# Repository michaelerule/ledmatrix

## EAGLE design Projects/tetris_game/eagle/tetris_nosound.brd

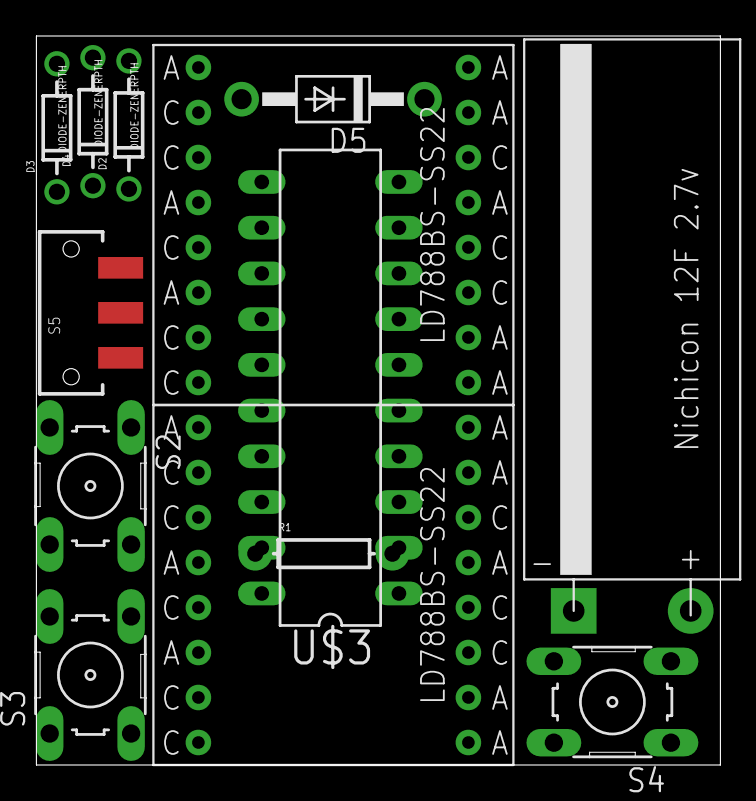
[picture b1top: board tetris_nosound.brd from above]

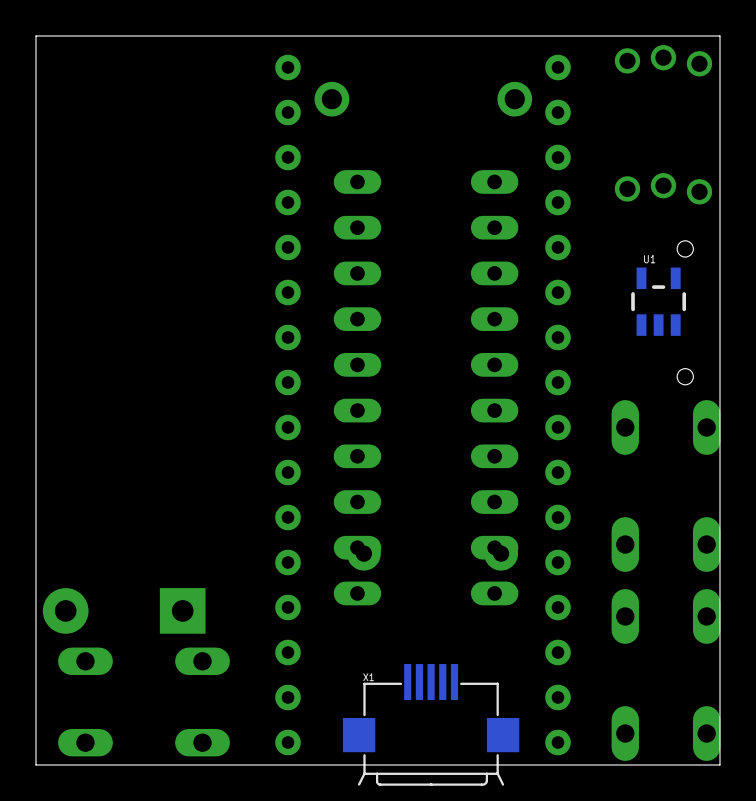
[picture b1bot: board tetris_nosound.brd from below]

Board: 2 copper layers, 38.0 x 40.5 mm, 15 parts (2 on the bottom side), 25 nets, no tracks yet.

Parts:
D2, D3, D4: DIODE-ZENERPTH; DIODE-ZENER
D5: 1N4004; DO41-10
R1: AXIAL-0.3
S2, S3, S4: B3F-10XX
S5: SWITCH-SPDT-SMD
U1: V_REG_LDOSMD; SOT23-5
U$1, U$2: LD788BS-SS22
U$3: TINY2313-*P*; DIL20
U$5: NICHICON_12F; NICHICON_10X30
X1: USB-MICROB

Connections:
unnamed: U$1.A4, U$2.C1, U$3.13
unnamed: U$1.A5, U$2.C2, U$3.14
unnamed: U$1.C6, U$2.A2, U$3.15
unnamed: U$1.A6, U$2.C3, U$3.16
unnamed: U$1.C7, U$2.A3, U$3.17
unnamed: U$1.A7, U$2.C4, U$3.19
unnamed: U$1.A8, U$2.C5, U$3.5
unnamed: U$1.C8, U$2.A1, U$3.18
unnamed: D5.C, R1.P$1, U$5.P$2
unnamed: U$1.C2, U$2.A5, U$3.3
unnamed: D2.P$2, U$1.A2, U$2.C6, U$3.6
unnamed: D3.P$2, U$1.C3, U$2.A6, U$3.7
unnamed: D4.P$2, U$1.A3, U$2.C7, U$3.8
unnamed: U$1.A1, U$2.C8, U$3.9
unnamed: U$1.C4, U$2.A7, U$3.11
unnamed: U$1.C5, U$2.A8, U$3.12
unnamed: D5.A, U$3.10
unnamed: S5.1, U1.5, U$5.P$1
unnamed: D2.P$1, S2.3, S2.4
unnamed: D3.P$1, S3.3, S3.4
unnamed: D4.P$1, S4.3, S4.4
unnamed: R1.P$2, U1.2, X1.GND
unnamed: U1.1, X1.D+, X1.D-, X1.VBUS
unnamed: S5.2, U$3.20
unnamed: S2.1, S2.2, S3.1, S3.2, S4.1, S4.2, U$1.C1, U$2.A4

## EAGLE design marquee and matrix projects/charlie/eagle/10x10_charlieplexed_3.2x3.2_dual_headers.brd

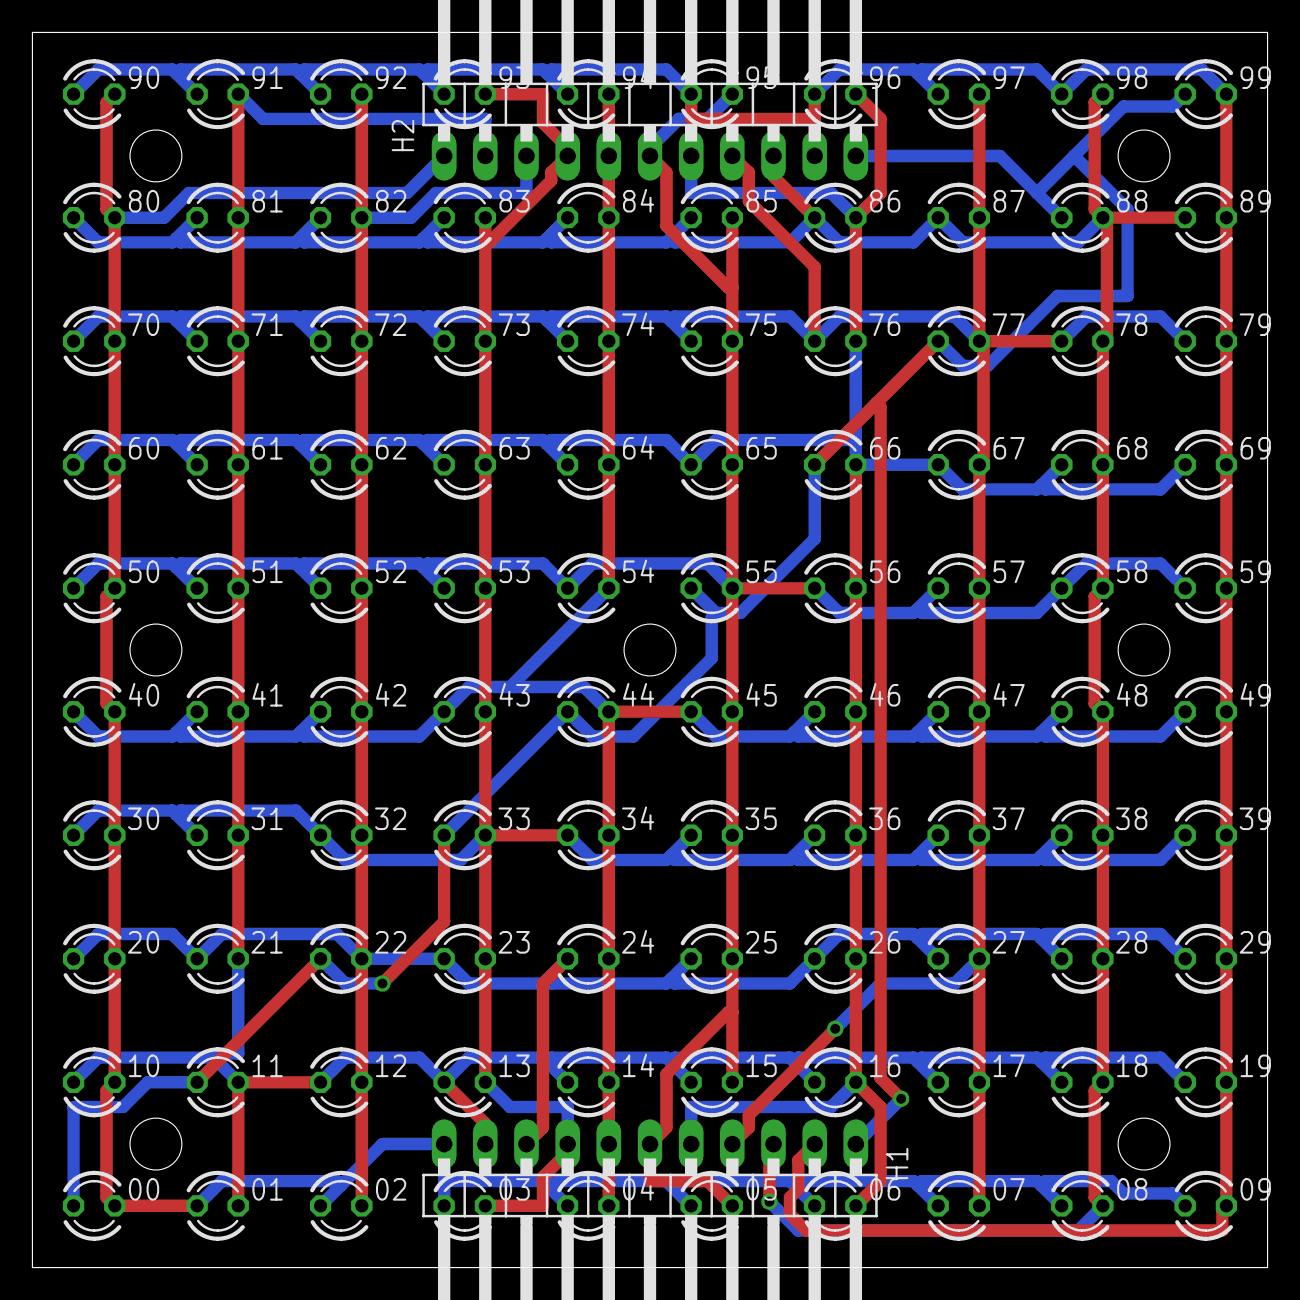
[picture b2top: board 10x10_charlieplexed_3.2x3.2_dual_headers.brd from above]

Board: 2 copper layers, 76.2 x 76.2 mm, 102 parts (0 on the bottom side), 11 nets.

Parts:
00, 01, 02, 03, 04, 05, 06, 07, 08, 09, 10, 11, 12, 13, 14, 15, 16, 17, 18, 19, 20, 21, 22, 23, 24, 25, 26, 27, 28, 29, 30, 31, 32, 33, 34, 35, 36, 37, 38, 39, 40, 41, 42, 43, 44, 45, 46, 47, 48, 49, 50, 51, 52, 53, 54, 55, 56, 57, 58, 59, 60, 61, 62, 63, 64, 65, 66, 67, 68, 69, 70, 71, 72, 73, 74, 75, 76, 77, 78, 79, 80, 81, 82, 83, 84, 85, 86, 87, 88, 89, 90, 91, 92, 93, 94, 95, 96, 97, 98, 99: LED3MM
H1, H2: 1X11/90

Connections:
D: 00.A, 11.A, 22.A, 33.A, 44.A, 55.A, 66.A, 77.A, 88.A, 99.A, H1.1, H2.11
S0: 00.K, 01.A, 02.A, 03.A, 04.A, 05.A, 06.A, 07.A, 08.A, 09.A, 10.K, 20.K, 30.K, 40.K, 50.K, 60.K, 70.K, 80.K, 90.K, H1.11, H2.1
S1: 01.K, 10.A, 11.K, 12.A, 13.A, 14.A, 15.A, 16.A, 17.A, 18.A, 19.A, 21.K, 31.K, 41.K, 51.K, 61.K, 71.K, 81.K, 91.K, H1.10, H2.2
S2: 02.K, 12.K, 20.A, 21.A, 22.K, 23.A, 24.A, 25.A, 26.A, 27.A, 28.A, 29.A, 32.K, 42.K, 52.K, 62.K, 72.K, 82.K, 92.K, H1.9, H2.3
S3: 03.K, 13.K, 23.K, 30.A, 31.A, 32.A, 33.K, 34.A, 35.A, 36.A, 37.A, 38.A, 39.A, 43.K, 53.K, 63.K, 73.K, 83.K, 93.K, H1.8, H2.4
S4: 04.K, 14.K, 24.K, 34.K, 40.A, 41.A, 42.A, 43.A, 44.K, 45.A, 46.A, 47.A, 48.A, 49.A, 54.K, 64.K, 74.K, 84.K, 94.K, H1.7, H2.5
S5: 05.K, 15.K, 25.K, 35.K, 45.K, 50.A, 51.A, 52.A, 53.A, 54.A, 55.K, 56.A, 57.A, 58.A, 59.A, 65.K, 75.K, 85.K, 95.K, H1.6, H2.6
S6: 06.K, 16.K, 26.K, 36.K, 46.K, 56.K, 60.A, 61.A, 62.A, 63.A, 64.A, 65.A, 66.K, 67.A, 68.A, 69.A, 76.K, 86.K, 96.K, H1.5, H2.7
S7: 07.K, 17.K, 27.K, 37.K, 47.K, 57.K, 67.K, 70.A, 71.A, 72.A, 73.A, 74.A, 75.A, 76.A, 77.K, 78.A, 79.A, 87.K, 97.K, H1.4, H2.8
S8: 08.K, 18.K, 28.K, 38.K, 48.K, 58.K, 68.K, 78.K, 80.A, 81.A, 82.A, 83.A, 84.A, 85.A, 86.A, 87.A, 88.K, 89.A, 98.K, H1.3, H2.9
S9: 09.K, 19.K, 29.K, 39.K, 49.K, 59.K, 69.K, 79.K, 89.K, 90.A, 91.A, 92.A, 93.A, 94.A, 95.A, 96.A, 97.A, 98.A, 99.K, H1.2, H2.10

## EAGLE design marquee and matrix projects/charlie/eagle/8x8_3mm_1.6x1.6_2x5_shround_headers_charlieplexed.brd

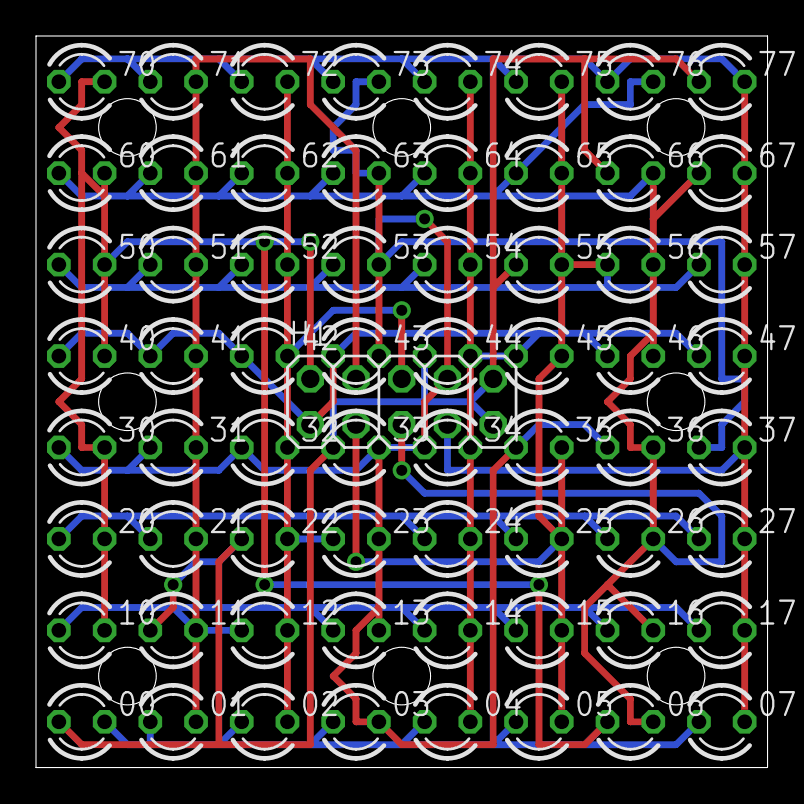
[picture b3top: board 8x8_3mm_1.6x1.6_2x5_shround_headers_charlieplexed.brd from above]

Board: 2 copper layers, 40.6 x 40.6 mm, 65 parts (0 on the bottom side), 9 nets.

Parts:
00, 01, 02, 03, 04, 05, 06, 07, 10, 11, 12, 13, 14, 15, 16, 17, 20, 21, 22, 23, 24, 25, 26, 27, 30, 31, 32, 33, 34, 35, 36, 37, 40, 41, 42, 43, 44, 45, 46, 47, 50, 51, 52, 53, 54, 55, 56, 57, 60, 61, 62, 63, 64, 65, 66, 67, 70, 71, 72, 73, 74, 75, 76, 77: LED3MM
H1: 2X05

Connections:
D: 00.A, 11.A, 22.A, 33.A, 44.A, 55.A, 66.A, 77.A, H1.9, H1.10
S0: 00.K, 01.A, 02.A, 03.A, 04.A, 05.A, 06.A, 07.A, 10.K, 20.K, 30.K, 40.K, 50.K, 60.K, 70.K, H1.2
S1: 01.K, 10.A, 11.K, 12.A, 13.A, 14.A, 15.A, 16.A, 17.A, 21.K, 31.K, 41.K, 51.K, 61.K, 71.K, H1.4
S2: 02.K, 12.K, 20.A, 21.A, 22.K, 23.A, 24.A, 25.A, 26.A, 27.A, 32.K, 42.K, 52.K, 62.K, 72.K, H1.6
S3: 03.K, 13.K, 23.K, 30.A, 31.A, 32.A, 33.K, 34.A, 35.A, 36.A, 37.A, 43.K, 53.K, 63.K, 73.K, H1.8
S4: 04.K, 14.K, 24.K, 34.K, 40.A, 41.A, 42.A, 43.A, 44.K, 45.A, 46.A, 47.A, 54.K, 64.K, 74.K, H1.1
S5: 05.K, 15.K, 25.K, 35.K, 45.K, 50.A, 51.A, 52.A, 53.A, 54.A, 55.K, 56.A, 57.A, 65.K, 75.K, H1.3
S6: 06.K, 16.K, 26.K, 36.K, 46.K, 56.K, 60.A, 61.A, 62.A, 63.A, 64.A, 65.A, 66.K, 67.A, 76.K, H1.5
S7: 07.K, 17.K, 27.K, 37.K, 47.K, 57.K, 67.K, 70.A, 71.A, 72.A, 73.A, 74.A, 75.A, 76.A, 77.K, H1.7

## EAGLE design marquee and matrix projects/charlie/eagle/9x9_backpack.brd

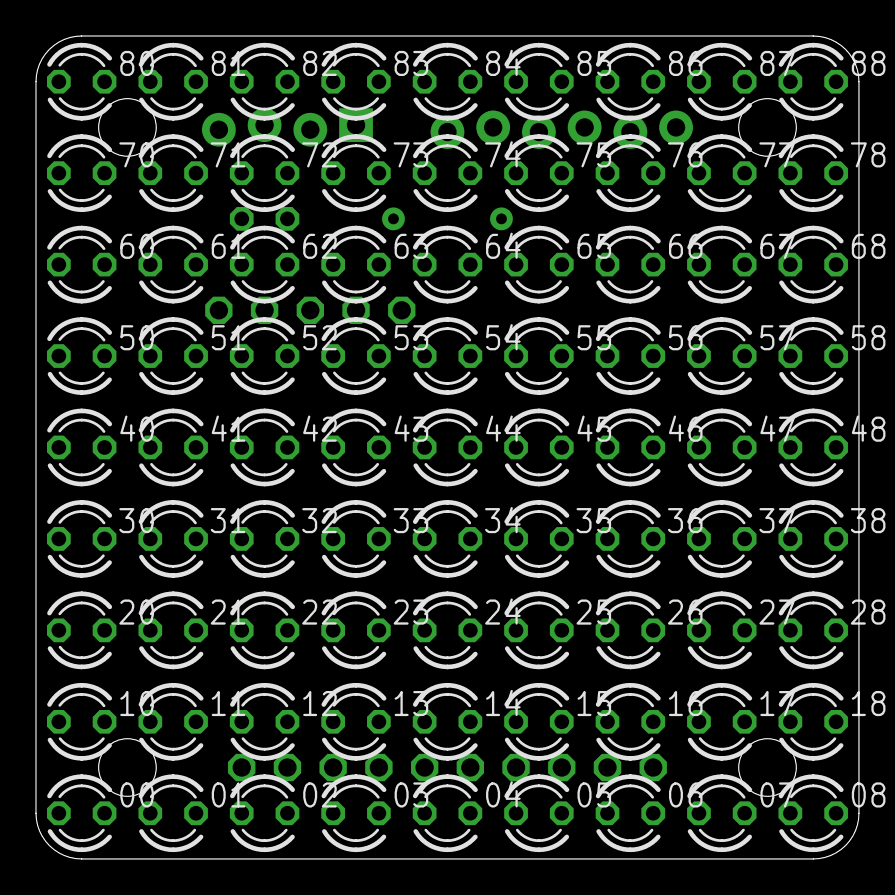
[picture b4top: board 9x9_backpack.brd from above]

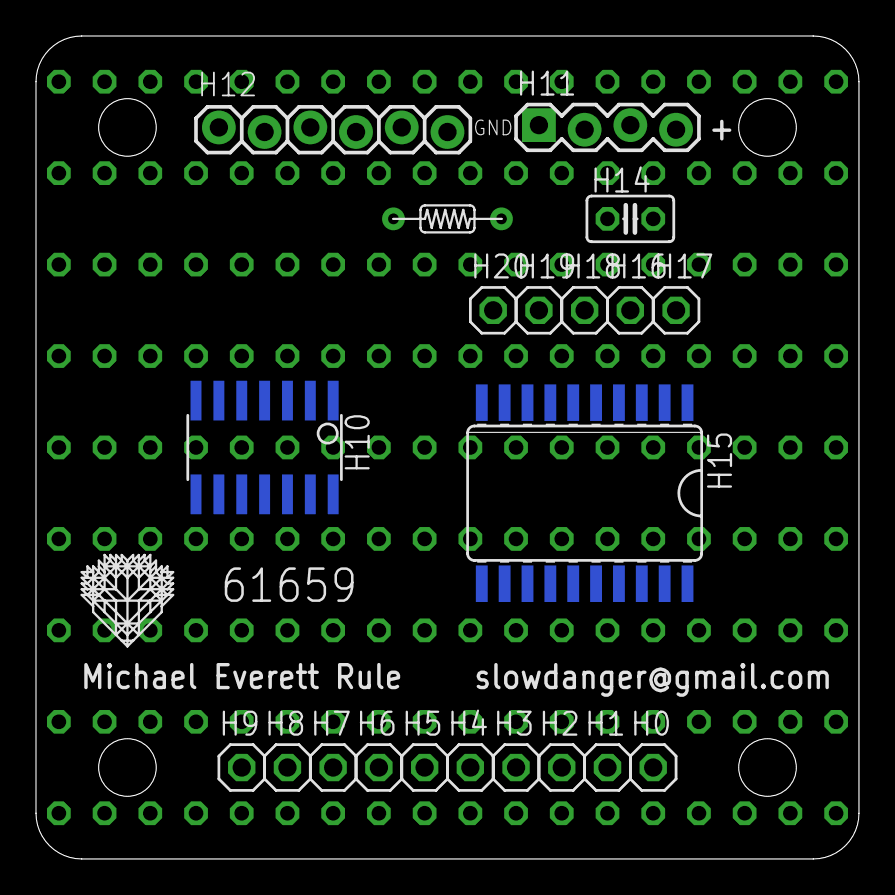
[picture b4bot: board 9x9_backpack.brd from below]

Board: 2 copper layers, 45.7 x 45.7 mm, 103 parts (22 on the bottom side), 20 nets, no tracks yet.

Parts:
00, 01, 02, 03, 04, 05, 06, 07, 08, 10, 11, 12, 13, 14, 15, 16, 17, 18, 20, 21, 22, 23, 24, 25, 26, 27, 28, 30, 31, 32, 33, 34, 35, 36, 37, 38, 40, 41, 42, 43, 44, 45, 46, 47, 48, 50, 51, 52, 53, 54, 55, 56, 57, 58, 60, 61, 62, 63, 64, 65, 66, 67, 68, 70, 71, 72, 73, 74, 75, 76, 77, 78, 80, 81, 82, 83, 84, 85, 86, 87, 88: LED3MM
H0, H1, H2, H3, H4, H5, H6, H7, H8, H9, H16, H17, H18, H19, H20: 1X01
H10: SOIC14
H11: 1X04_LOCK
H12: 1X06_LOCK
H13: R-6
H14: C025-025X050
H15: SO20L
H21: LOGO

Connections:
D: 00.A, 11.A, 22.A, 33.A, 44.A, 55.A, 66.A, 77.A, 88.A, H9.1, H10.8, H12.5, H15.18
S0: 00.K, 01.A, 02.A, 03.A, 04.A, 05.A, 06.A, 07.A, 08.A, 10.K, 20.K, 30.K, 40.K, 50.K, 60.K, 70.K, 80.K, H0.1, H10.3, H15.9
S1: 01.K, 10.A, 11.K, 12.A, 13.A, 14.A, 15.A, 16.A, 17.A, 18.A, 21.K, 31.K, 41.K, 51.K, 61.K, 71.K, 81.K, H1.1, H10.5, H15.16
S2: 02.K, 12.K, 20.A, 21.A, 22.K, 23.A, 24.A, 25.A, 26.A, 27.A, 28.A, 32.K, 42.K, 52.K, 62.K, 72.K, 82.K, H2.1, H10.6, H15.15
S3: 03.K, 13.K, 23.K, 30.A, 31.A, 32.A, 33.K, 34.A, 35.A, 36.A, 37.A, 38.A, 43.K, 53.K, 63.K, 73.K, 83.K, H3.1, H10.7, H12.1, H15.17
S4: 04.K, 14.K, 24.K, 34.K, 40.A, 41.A, 42.A, 43.A, 44.K, 45.A, 46.A, 47.A, 48.A, 54.K, 64.K, 74.K, 84.K, H4.1, H10.13, H15.14
S5: 05.K, 15.K, 25.K, 35.K, 45.K, 50.A, 51.A, 52.A, 53.A, 54.A, 55.K, 56.A, 57.A, 58.A, 65.K, 75.K, 85.K, H5.1, H10.12, H15.13
S6: 06.K, 16.K, 26.K, 36.K, 46.K, 56.K, 60.A, 61.A, 62.A, 63.A, 64.A, 65.A, 66.K, 67.A, 68.A, 76.K, 86.K, H6.1, H10.11, H15.12
S7: 07.K, 17.K, 27.K, 37.K, 47.K, 57.K, 67.K, 70.A, 71.A, 72.A, 73.A, 74.A, 75.A, 76.A, 77.K, 78.A, 87.K, H7.1, H10.10, H15.11
S8: 08.K, 18.K, 28.K, 38.K, 48.K, 58.K, 68.K, 78.K, 80.A, 81.A, 82.A, 83.A, 84.A, 85.A, 86.A, 87.A, 88.K, H8.1, H10.9, H12.2, H15.19
S$1: H10.14, H11.1, H12.6, H14.1, H15.10
S$2: H10.1, H11.4, H12.4, H13.P$2, H14.2, H15.20
S$3: H10.4, H12.3, H13.P$1, H15.1
S$4: H10.2, H11.2, H15.2
S$5: H11.3, H15.3
S$6: H15.8, H20.1
S$7: H15.7, H19.1
S$8: H15.6, H18.1
S$9: H15.5, H16.1
S$10: H15.4, H17.1

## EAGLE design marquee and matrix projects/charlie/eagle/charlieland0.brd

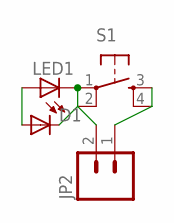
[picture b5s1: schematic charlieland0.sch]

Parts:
D1: DIODE1N4148; DIODE-1N4148
JP2: M02; 1X02_LONGPADS
LED1: LED5MM
S1: TAC_SWITCHPTH; TACTILE-PTH

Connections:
unnamed: D1.C, JP2.2, LED1.K (C), S1.1, S1.2
unnamed: JP2.1, S1.3, S1.4
unnamed: D1.A, LED1.A

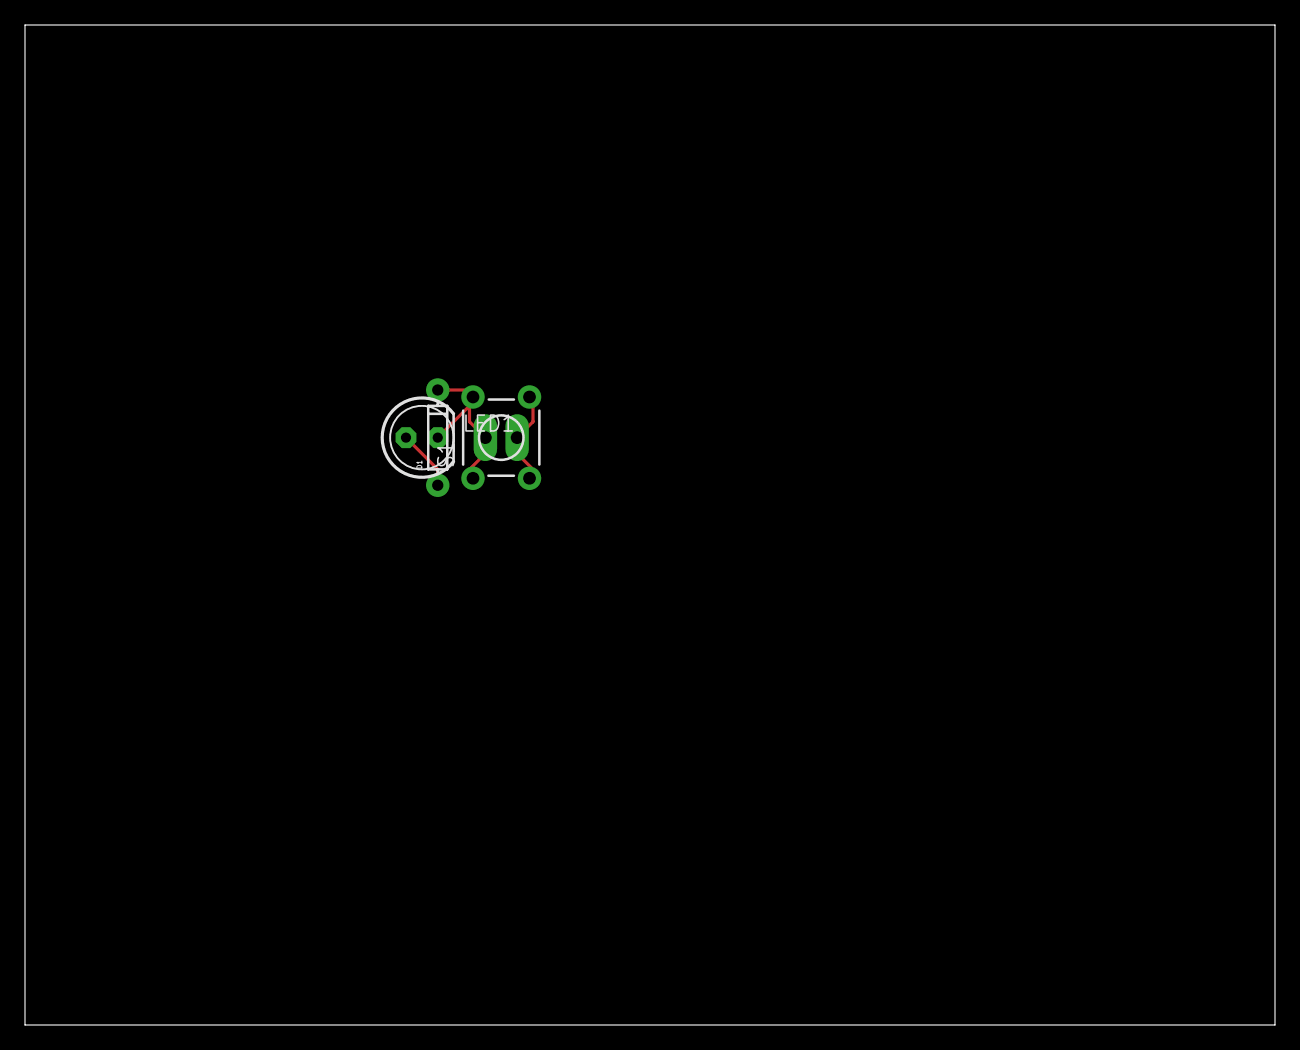
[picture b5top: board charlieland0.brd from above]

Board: 2 copper layers, 100.0 x 80.0 mm, 4 parts (1 on the bottom side), 3 nets.

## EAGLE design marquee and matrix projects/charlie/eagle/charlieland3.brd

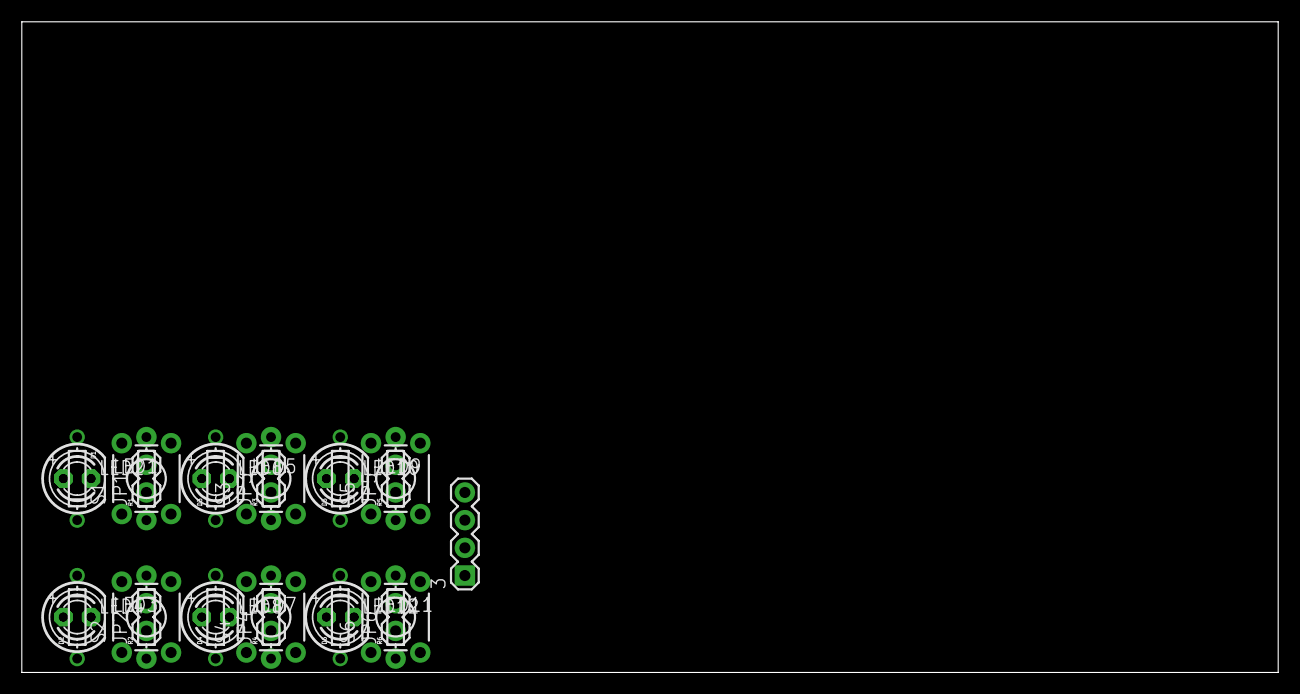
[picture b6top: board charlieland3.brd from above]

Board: 2 copper layers, 115.2 x 59.7 mm, 37 parts (0 on the bottom side), 9 nets, no tracks yet.

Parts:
3: 1X04
D1, D2, D3, D4, D5, D6: DO-1N4148
JP1, JP2, JP3, JP4, JP5, JP6: 1X02
LED1, LED3, LED5, LED7, LED9, LED11: LED5MM
LED2, LED4, LED6, LED8, LED10, LED12: LED3MM
R1, R2, R3, R4, R5, R6: AXIAL-0.3
S1, S2, S3, S4, S5, S6: TACTILE-PTH

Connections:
1: 3.1, D2.C, D4.C, JP1.2, JP3.2, LED3.K, LED4.K, LED7.K, LED8.K, R1.P$1, R3.P$1, S1.3, S1.4, S3.3, S3.4
2: 3.2, D1.C, D3.C, D6.C, JP2.2, JP4.2, JP5.2, LED1.K, LED2.K, LED5.K, LED6.K, LED11.K, LED12.K, R2.P$1, R4.P$1, R5.P$1, S2.3, S2.4, S4.3, S4.4, S5.3, S5.4
3: 3.3, D5.C, JP6.2, LED9.K, LED10.K, R6.P$1, S6.3, S6.4
unnamed: D3.A, JP3.1, LED5.A, LED6.A, R3.P$2, S3.1, S3.2
unnamed: D4.A, JP4.1, LED7.A, LED8.A, R4.P$2, S4.1, S4.2
unnamed: D1.A, JP1.1, LED1.A, LED2.A, R1.P$2, S1.1, S1.2
unnamed: D2.A, JP2.1, LED3.A, LED4.A, R2.P$2, S2.1, S2.2
unnamed: D5.A, JP5.1, LED9.A, LED10.A, R5.P$2, S5.1, S5.2
unnamed: D6.A, JP6.1, LED11.A, LED12.A, R6.P$2, S6.1, S6.2

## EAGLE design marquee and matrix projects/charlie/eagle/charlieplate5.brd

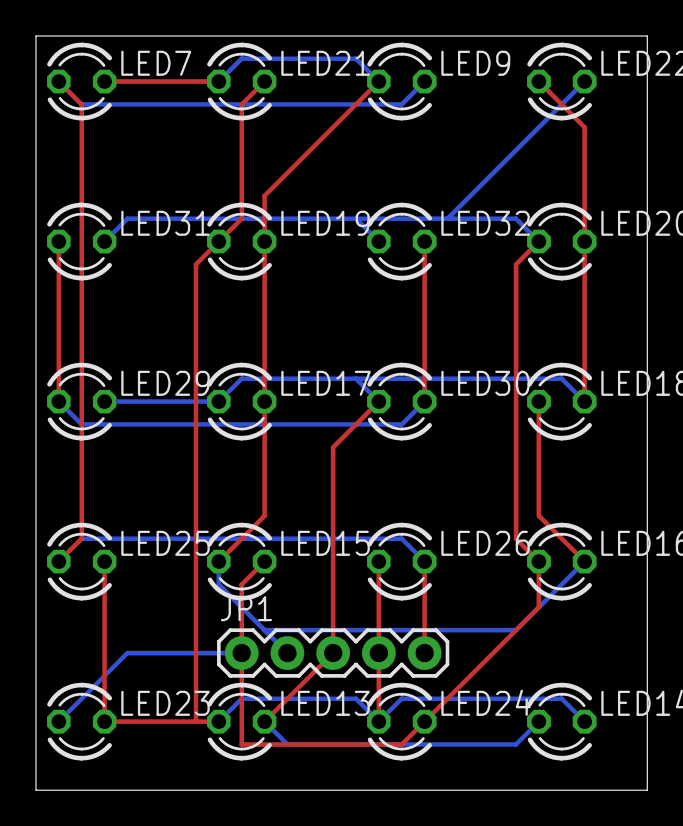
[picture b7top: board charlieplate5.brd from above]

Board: 2 copper layers, 34.0 x 41.9 mm, 21 parts (0 on the bottom side), 6 nets.

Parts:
JP1: 1X05
LED7, LED9, LED13, LED14, LED15, LED16, LED17, LED18, LED19, LED20, LED21, LED22, LED23, LED24, LED25, LED26, LED29, LED30, LED31, LED32: LED3MM

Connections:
unnamed: LED29.A, LED30.K, LED31.A, LED32.K
unnamed: JP1.1, LED15.K, LED16.A, LED20.A, LED22.K, LED23.A, LED24.K, LED31.K, LED32.A
unnamed: JP1.3, LED13.K, LED14.A, LED17.A, LED18.K, LED20.K, LED22.A, LED29.K, LED30.A
unnamed: JP1.4, LED13.A, LED14.K, LED19.A, LED21.K, LED23.K, LED24.A, LED25.K, LED26.A
unnamed: JP1.5, LED7.A, LED9.K, LED25.A, LED26.K
unnamed: JP1.2, LED7.K, LED9.A, LED15.A, LED16.K, LED17.K, LED18.A, LED19.K, LED21.A

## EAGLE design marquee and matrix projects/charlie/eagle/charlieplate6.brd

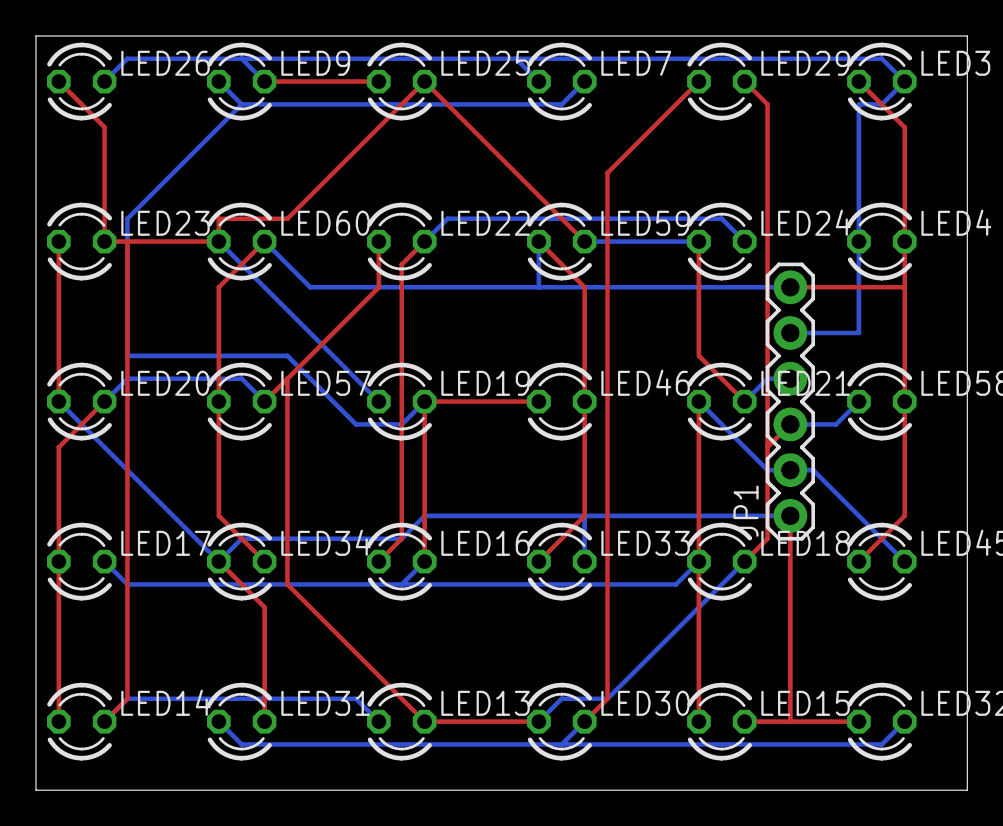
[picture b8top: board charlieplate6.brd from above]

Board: 2 copper layers, 51.7 x 41.9 mm, 31 parts (0 on the bottom side), 7 nets.

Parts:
JP1: 1X06
LED3, LED4, LED7, LED9, LED13, LED14, LED15, LED16, LED17, LED18, LED19, LED20, LED21, LED22, LED23, LED24, LED25, LED26, LED29, LED30, LED31, LED32, LED33, LED34, LED45, LED46, LED57, LED58, LED59, LED60: LED3MM

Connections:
unnamed: LED29.A, LED30.K, LED31.A, LED32.K
unnamed: JP1.1, LED15.K, LED16.A, LED20.A, LED22.K, LED23.A, LED24.K, LED31.K, LED32.A, LED33.K, LED34.A
unnamed: JP1.3, LED13.K, LED14.A, LED17.A, LED18.K, LED20.K, LED22.A, LED29.K, LED30.A, LED57.K, LED58.A
unnamed: JP1.6, LED3.A, LED4.K, LED33.A, LED34.K, LED45.A, LED46.K, LED57.A, LED58.K, LED59.A, LED60.K
unnamed: JP1.4, LED13.A, LED14.K, LED19.A, LED21.K, LED23.K, LED24.A, LED25.K, LED26.A, LED59.K, LED60.A
unnamed: JP1.5, LED3.K, LED4.A, LED7.A, LED9.K, LED25.A, LED26.K
unnamed: JP1.2, LED7.K, LED9.A, LED15.A, LED16.K, LED17.K, LED18.A, LED19.K, LED21.A, LED45.K, LED46.A

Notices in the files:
parts and their libraries:
SparkFun: Licensing: CC v3.0 Share-Alike You are welcome to use this library for commercial purposes.
